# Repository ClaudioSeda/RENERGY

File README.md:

# RENERGY

## Description

RENERGY is a library for managing and monitoring renewable energy systems. It provides functionalities to interface with various sensors and devices to collect data and control energy systems.

## Installation

To install the RENERGY library in the Arduino IDE, follow these steps:

1. Download the RENERGY library from the [GitHub repository](https://github.com/ClaudioSeda/RENERGY).
2. Open the Arduino IDE.
3. Go to `Sketch` -> `Include Library` -> `Add .ZIP Library...`.
4. Select the downloaded RENERGY library ZIP file.
5. The library is now installed and ready to use.

## Usage with ESP32

To use the RENERGY library with ESP32, follow these steps:

1. Connect the sensors and devices to the appropriate pins on the ESP32 board.
2. Include the RENERGY library in your sketch:
    ```cpp
    #include <RENERGY.h>
    ```
3. Create an instance of the RENERGY class:
    ```cpp
    RENERGY renergy;
    ```
4. Initialize the RENERGY library in the `setup` function:
    ```cpp
    void setup() {
        Serial.begin(115200);
        renergy.begin();
    }
    ```
5. Use the library functions to collect data and control the energy system in the `loop` function:
    ```cpp
    void loop() {
        float voltage = renergy.getVoltage();
        float current = renergy.getCurrent();

        Serial.print("Voltage: ");
        Serial.print(voltage);
        Serial.print(" V");
        Serial.print("Current: ");
        Serial.print(current);
        Serial.println(" A");

        // Add your custom code to control the energy system
    }
    ```

For more detailed examples, refer to the `examples` folder in the repository.

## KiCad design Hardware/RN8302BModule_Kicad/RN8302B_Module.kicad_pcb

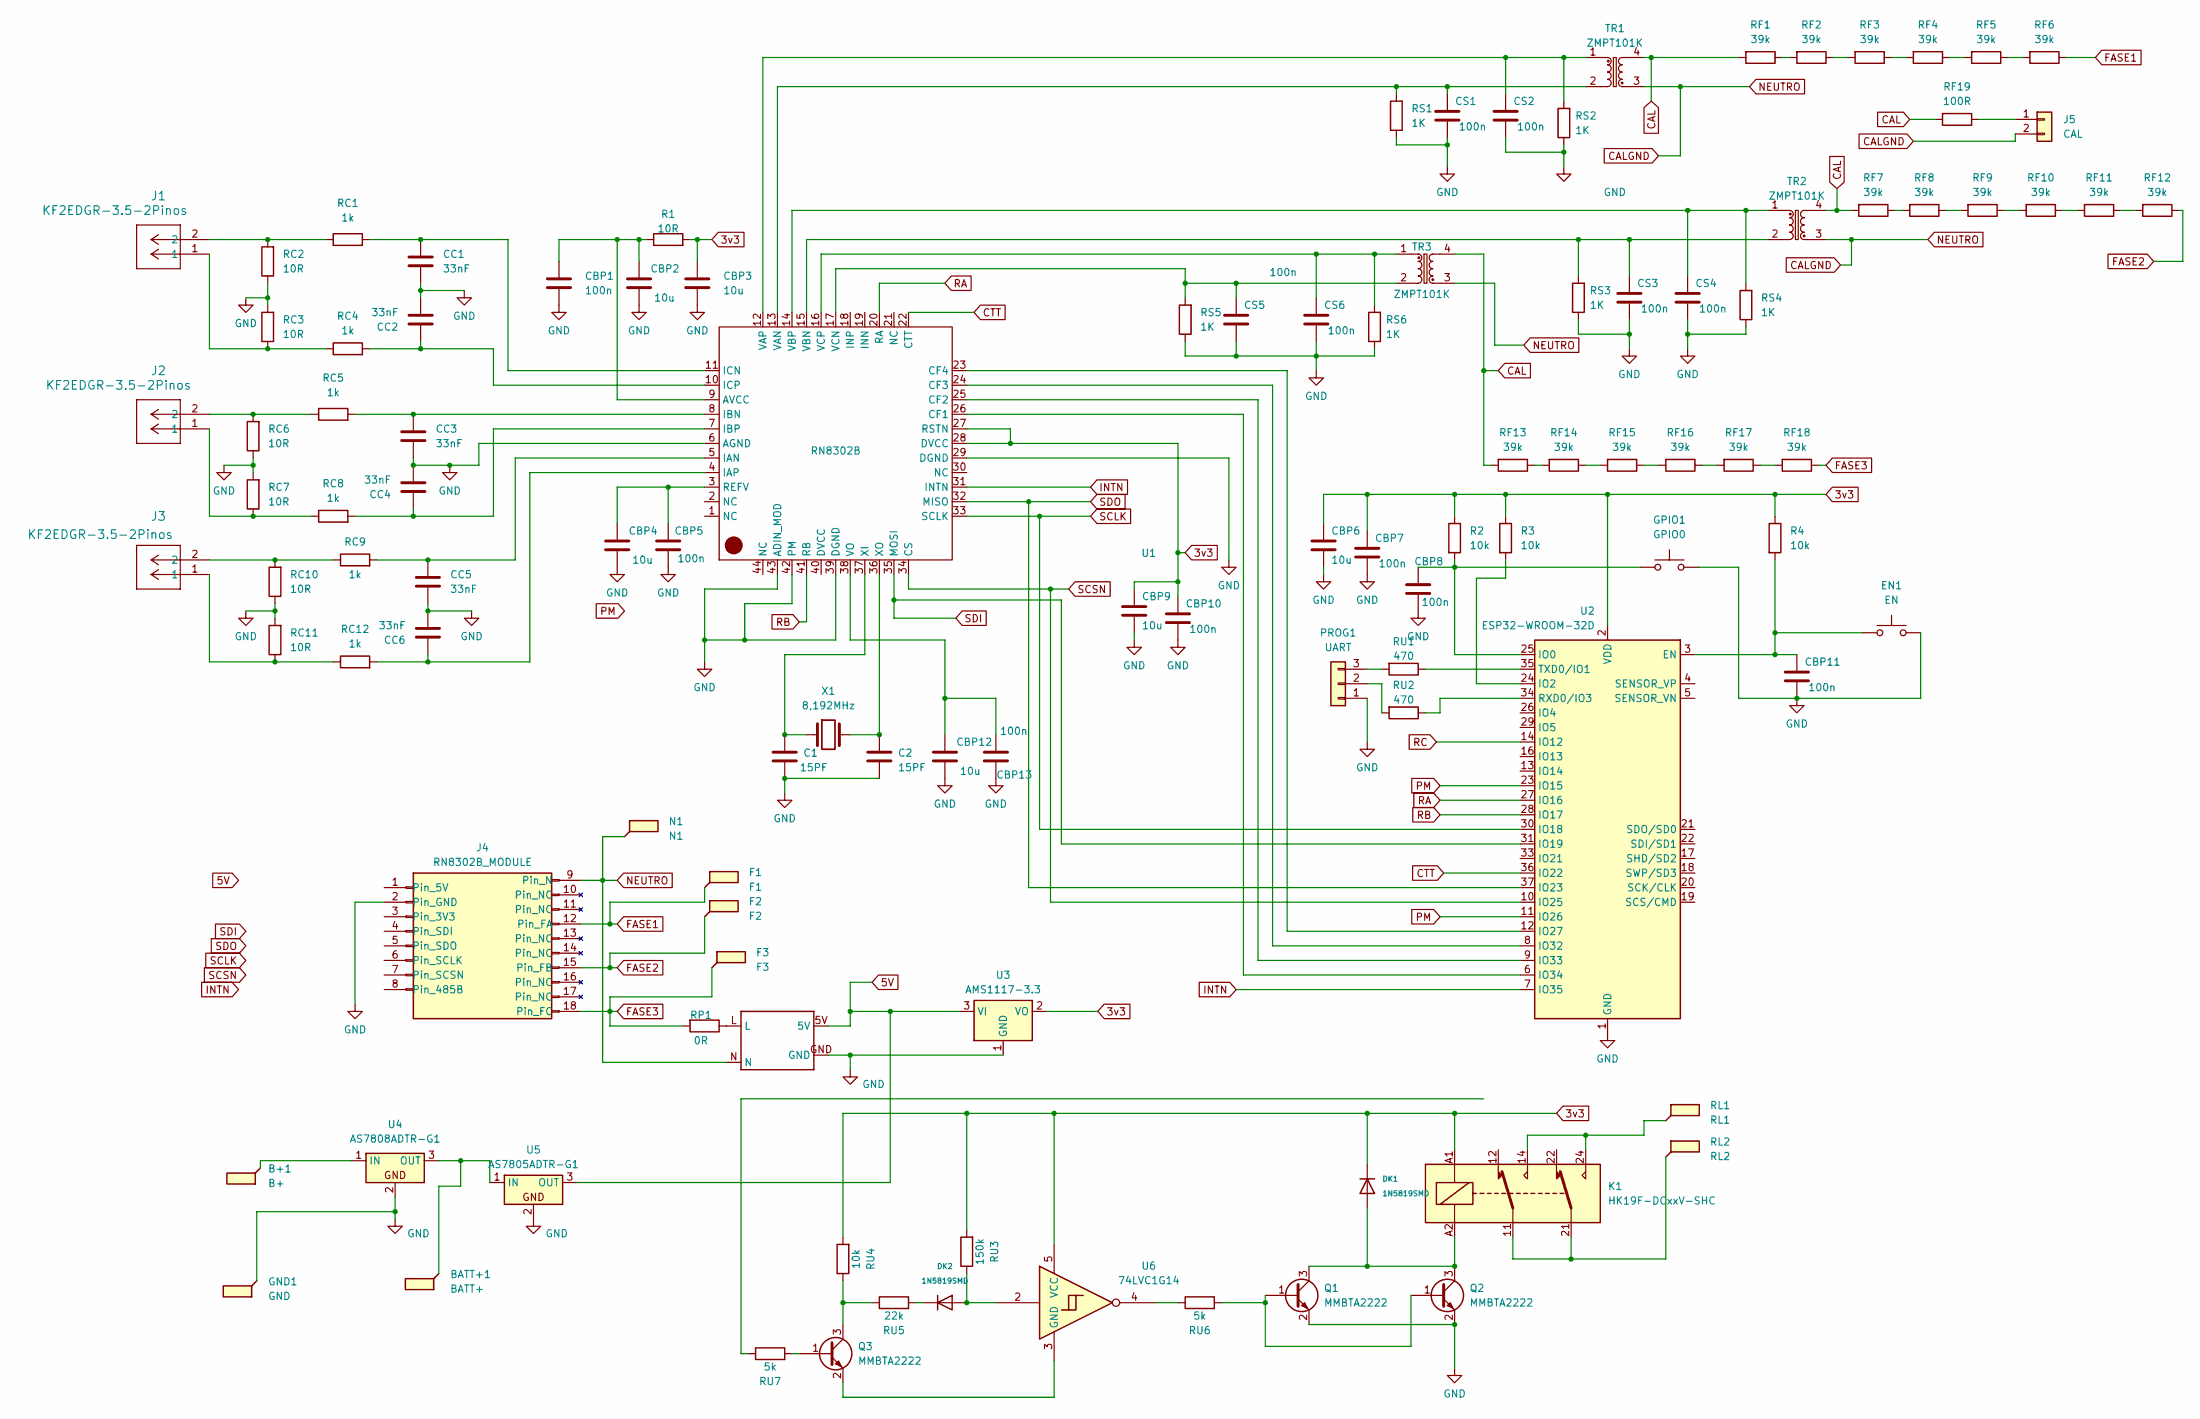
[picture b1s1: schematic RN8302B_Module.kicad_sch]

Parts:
B+1: B+; TestPoint_Plated_Hole_D2.0mm
BATT+1: BATT+; TestPoint_Plated_Hole_D2.0mm
C1: 15PF; C_0603_1608Metric_Pad1.08x0.95mm_HandSolder
C2: 15PF; C0603
CBP1, CBP5, CBP7, CBP8, CBP10, CBP11, CBP13: 100n; C_0805_2012Metric_Pad1.18x1.45mm_HandSolder
CBP2, CBP3, CBP4, CBP6, CBP9, CBP12: 10u; C_0805_2012Metric_Pad1.18x1.45mm_HandSolder
CC1, CC2, CC3, CC4, CC5, CC6: 33nF; C_0805_2012Metric_Pad1.18x1.45mm_HandSolder
CS1, CS2, CS3, CS4, CS5, CS6: 100n; C_0805_2012Metric_Pad1.18x1.45mm_HandSolder
DK1, DK2: 1N5819SMD; DIODE_0805
EN1: EN; SW_SPST_TL3342
F1: F1; TestPoint_Plated_Hole_D2.0mm
F2: F2; TestPoint_Plated_Hole_D2.0mm
F3: F3; TestPoint_Plated_Hole_D2.0mm
GND1: GND; TestPoint_Plated_Hole_D2.0mm
GPIO1: GPIO0; SW_SPST_TL3342
J1, J2, J3: KF2EDGR-3.5-2Pinos; CONN_KF2EDGR-3.5-2P_CKE
J4: RN8302B_MODULE; JSY-MK333Module
J5: CAL
K1: HK19F-DCxxV-SHC; Relay_DPDT_Finder_30.22
N1: N1; TestPoint_Plated_Hole_D2.0mm
PROG1: UART; PinHeader_1x03_P2.54mm_Vertical
Q1, Q2, Q3: MMBTA2222; SOT-23
R1: 10R; R_0805_2012Metric_Pad1.20x1.40mm_HandSolder
R2, R3, R4: 10k; R_0805_2012Metric_Pad1.20x1.40mm_HandSolder
RC1, RC4, RC5, RC8, RC9, RC12: 1k; R_0805_2012Metric_Pad1.20x1.40mm_HandSolder
RC2, RC3, RC6, RC7, RC10, RC11: 10R; R_0805_2012Metric_Pad1.20x1.40mm_HandSolder
RF1, RF2, RF3, RF4, RF5, RF6, RF7, RF8, RF9, RF10, RF11, RF12, RF13, RF14, RF15, RF16, RF17, RF18: 39k; C1206
RF19: 100R; C1206
RL1: RL1; TestPoint_Plated_Hole_D2.0mm
RL2: RL2; TestPoint_Plated_Hole_D2.0mm
RP1: 0R; C1206
RS1, RS2, RS3, RS4, RS5, RS6: 1K; R_0805_2012Metric_Pad1.20x1.40mm_HandSolder
RU1, RU2: 470; R_0805_2012Metric_Pad1.20x1.40mm_HandSolder
RU3: 150k; R_0805_2012Metric_Pad1.20x1.40mm_HandSolder
RU4: 10k; R_0805_2012Metric_Pad1.20x1.40mm_HandSolder
RU5: 22k; R_0805_2012Metric_Pad1.20x1.40mm_HandSolder
RU6, RU7: 5k; R_0805_2012Metric_Pad1.20x1.40mm_HandSolder
TR1, TR2, TR3: ZMPT101K; Transformer_Zeming_ZMPT101K
U1: RN8302B; LQFP-44_10x10mm_P0.8mm; MANUFACTURER PART RN8302B; JLCPCB PART CLASS Extended Part
U2: ESP32-WROOM-32D
U3: AMS1117-3.3; SOT-223-3_TabPin2
U4: AS7808ADTR-G1; TO-252-2
U5: AS7805ADTR-G1; TO-252-2
U6: 74LVC1G14; SOT-23-5
U$1: 5VSMPSVERT; 5VSMPS-VERT
X1: 8,192MHz; Crystal_HC49-4H_Vertical

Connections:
3v3: CBP3.1, CBP6.1, CBP7.1, CBP9.1, CBP10.1, DK1.1 (K), K1.A1, R1.2, R2.1, R3.1, R4.1, RU3.2, RU4.2, U1.27 (RSTN), U1.28 (DVCC), U2.2 (VDD), U3.2 (VO), U6.5 (VCC)
5V: U3.3 (VI), U5.3 (OUT), U$1.5V
CAL: RF1.2, RF7.2, RF13.2, RF19.2, TR1.4, TR2.4, TR3.4
CALGND: J4.9 (Pin_N), J5.2, N1.1, TR1.3, TR2.3, TR3.3, U$1.N
CTT: U1.22 (CTT), U2.36 (IO22)
FASE1: F1.1, J4.12 (Pin_FA), RF6.1
FASE2: F2.1, J4.15 (Pin_FB), RF12.1
FASE3: F3.1, J4.18 (Pin_FC), RF18.1, RP1.2
GND: C1.2, C2.2, CBP1.2, CBP2.2, CBP3.2, CBP4.2, CBP5.2, CBP6.2, CBP7.2, CBP8.2, CBP9.2, CBP10.2, CBP11.2, CBP12.2, CBP13.2, CC1.2, CC2.2, CC3.2, CC4.2, CC5.2, CC6.2, CS1.2, CS2.2, CS3.2, CS4.2, CS5.2, CS6.2, EN1.2, GND1.1, GPIO1.2, J4.2 (Pin_GND), PROG1.1, Q1.2 (E), Q2.2 (E), RC2.1, RC3.2, RC6.1, RC7.2, RC10.1, RC11.2, RS1.1, RS2.1, RS3.1, RS4.1, RS5.1, RS6.1, U1.6 (AGND), U1.29 (DGND), U1.39 (DGND), U1.42 (PM), U1.43 (ADIN_MOD), U2.1 (GND), U2.15 (GND), U2.38 (GND), U2.39 (GND), U3.1 (GND), U4.2, U5.2, U$1.GND
INTN: U1.31 (INTN), U2.7 (IO35)
unnamed: DK1.2 (A), K1.A2, Q1.3 (C), Q2.3 (C)
unnamed: DK2.2 (A), RU3.1, U6.2
unnamed: DK2.1 (K), RU5.2
unnamed: J1.1, RC3.1, RC4.1
unnamed: J1.2, RC1.1, RC2.2
unnamed: J2.1, RC7.1, RC8.1
unnamed: J2.2, RC5.1, RC6.2
unnamed: J3.1, RC11.1, RC12.1
unnamed: J3.2, RC9.1, RC10.2
unnamed: J5.1, RF19.1
unnamed: K1.11, K1.21, RL2.1
unnamed: K1.14, K1.24, RL1.1
unnamed: PROG1.2, RU2.2
unnamed: PROG1.3, RU1.2
unnamed: Q1.1 (B), Q2.1 (B), RU6.2
unnamed: Q3.1 (B), RU7.2
unnamed: Q3.3 (C), RU4.1, RU5.1
unnamed: Q3.2 (E), U6.3 (GND)
unnamed: RF1.1, RF2.2
unnamed: RF2.1, RF3.2
unnamed: RF3.1, RF4.2
unnamed: RF4.1, RF5.2
unnamed: RF5.1, RF6.2
unnamed: RF7.1, RF8.2
unnamed: RF8.1, RF9.2
unnamed: RF10.1, RF11.2
unnamed: RF9.1, RF10.2
unnamed: RF11.1, RF12.2
unnamed: RF13.1, RF14.2
unnamed: RF14.1, RF15.2
unnamed: RF15.1, RF16.2
unnamed: RF16.1, RF17.2
unnamed: RF17.1, RF18.2
unnamed: RP1.1, U$1.L
unnamed: RU6.1, U6.4
unnamed: CBP1.1, CBP2.1, R1.1, U1.9 (AVCC)
unnamed: U1.26 (CF1), U2.6 (IO34)
unnamed: U1.25 (CF2), U2.9 (IO33)
unnamed: U1.24 (CF3), U2.8 (IO32)
unnamed: U1.23 (CF4), U2.12 (IO27)
unnamed: CC5.1, RC9.2, U1.5 (IAN)
unnamed: CC6.1, RC12.2, U1.4 (IAP)
unnamed: CC3.1, RC5.2, U1.8 (IBN)
unnamed: CC4.1, RC8.2, U1.7 (IBP)
unnamed: CC1.1, RC1.2, U1.11 (ICN)
unnamed: CC2.1, RC4.2, U1.10 (ICP)
unnamed: CBP4.1, CBP5.1, U1.3 (REFV)
unnamed: CS1.1, RS1.2, TR1.2, U1.13 (VAN)
unnamed: CS2.1, RS2.2, TR1.1, U1.12 (VAP)
unnamed: CS3.1, RS3.2, TR2.2, U1.15 (VBN)
unnamed: CS4.1, RS4.2, TR2.1, U1.14 (VBP)
unnamed: CS5.1, RS5.2, TR3.2, U1.17 (VCN)
unnamed: CS6.1, RS6.2, TR3.1, U1.16 (VCP)
unnamed: CBP12.1, CBP13.1, U1.38 (VO)
unnamed: C1.1, U1.37 (XI), X1.1
unnamed: C2.1, U1.36 (XO), X1.2
unnamed: CBP11.1, EN1.1, R4.2, U2.3 (EN)
unnamed: CBP8.1, GPIO1.1, R2.2, U2.25 (IO0)
unnamed: R3.2, U2.24 (IO2)
unnamed: RU2.1, U2.34 (RXD0/IO3)
unnamed: RU1.1, U2.35 (TXD0/IO1)
unnamed: B+1.1, U4.1 (IN)
unnamed: BATT+1.1, U4.3 (OUT), U5.1 (IN)
PM: U2.11 (IO26), U2.23 (IO15)
RA: U1.20 (RA), U2.27 (IO16)
RB: U1.41 (RB), U2.28 (IO17)
RC: U2.14 (IO12)
SCLK: U1.33 (SCLK), U2.30 (IO18)
SCSN: U1.34 (CS), U2.10 (IO25)
SDI: U1.35 (MOSI), U2.31 (IO19)
SDO: U1.32 (MISO), U2.37 (IO23)

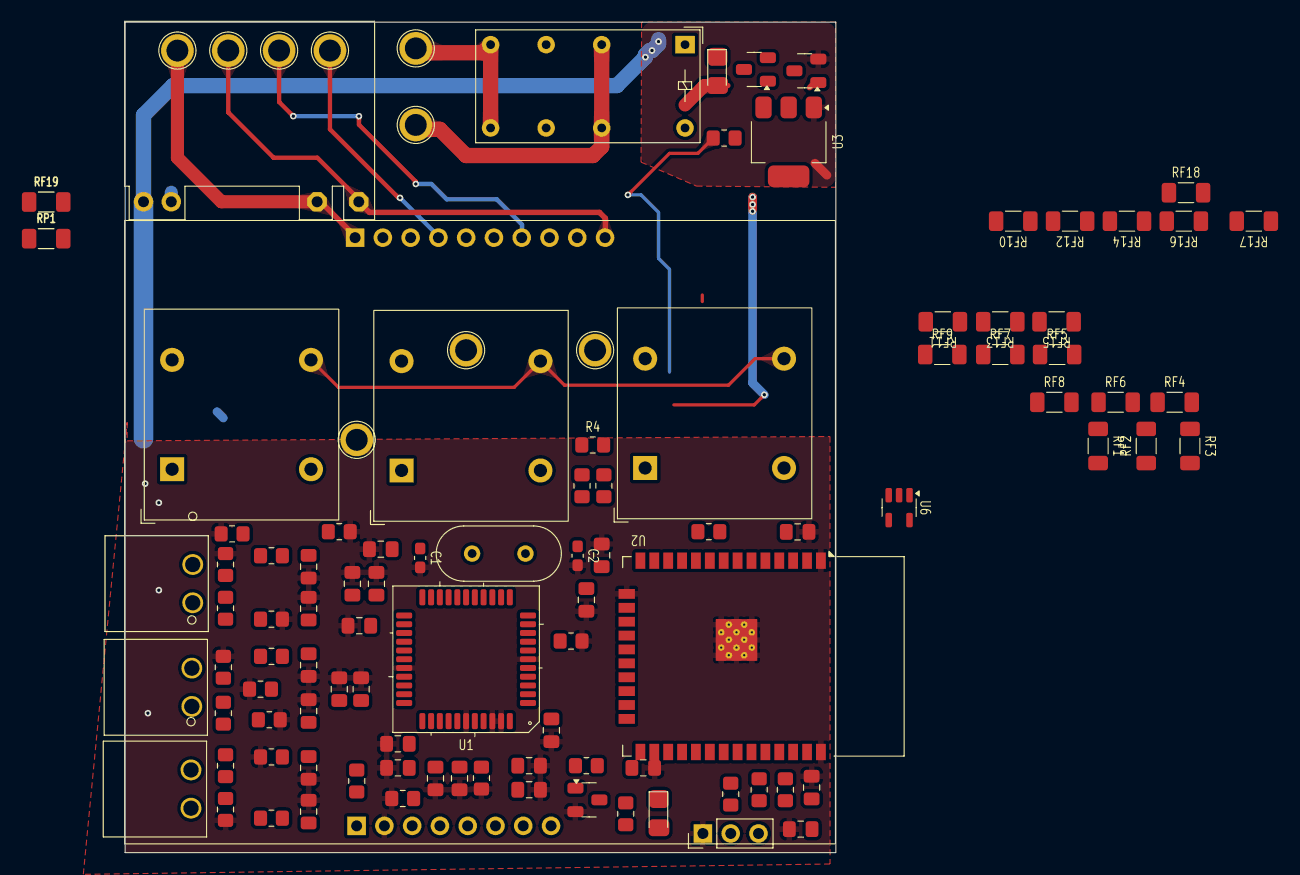
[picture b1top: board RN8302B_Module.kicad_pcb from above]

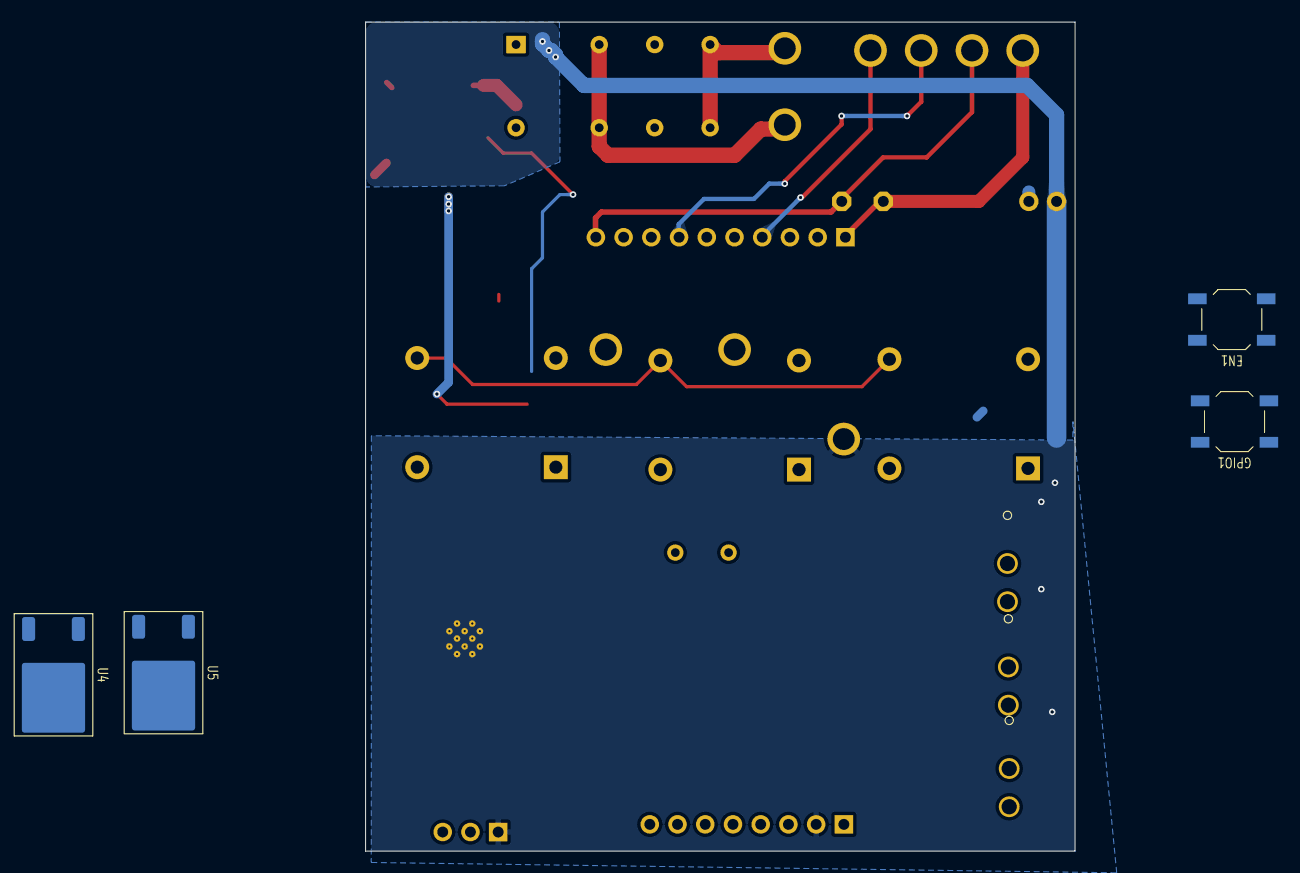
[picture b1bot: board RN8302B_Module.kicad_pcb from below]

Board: 2 copper layers, 65.0 x 76.0 mm, 109 parts (4 on the bottom side), 79 nets.

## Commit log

2025-05-01 Add Arduino library for ESP32
    ---
    For more details, open the [Copilot Workspace session](https://copilot-workspace.githubnext.com/ClaudioSeda/RENERGY?shareId=XXXX-XXXX-XXXX-XXXX).
2025-05-01 Complete example
2025-05-01 Complete Usage
2025-05-01 Add methods for additional sensor readings in `RENERGY` class
    * Add methods to `RENERGY.h` for real power, apparent power, energy in kWh, power factor, and frequency
    * Implement methods in `RENERGY.cpp` to return placeholder values for real power, apparent power, energy in kWh, power factor, and frequency
2025-05-01 Add additional data collection and alarms to BasicUsage example sketch
    * Collect additional data from sensors: real power, apparent power, energy in kWh, power factor, and frequency.
    * Print additional data to the serial monitor.
    * Add voltage and current alarms with corresponding messages for high and low values.
2025-05-01 Update library to include additional metering functions
    Add new functions to measure apparent power, real power, power factor, and frequency.
    * **RENERGY.h**
    - Add function declarations for `getApparentPower`, `getRealPower`, `getPowerFactor`, and `getFrequency`.
    * **RENERGY.cpp**
    - Implement functions `getApparentPower`, `getRealPower`, `getPowerFactor`, and `getFrequency`.
    * **BasicUsage.ino**
2025-05-04 Create RN8302B
2025-05-04 Add files via upload
    RN8301 Datasheet
2025-05-10 Atualiza estrutura
    Organizado
2025-06-27 Create d
2025-06-27 Create c
